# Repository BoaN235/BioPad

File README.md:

# BioPad
A 12 key macropad with a oled display and 5 LEDS uses KMK firmware. It is supposed to be a used during work to 

## Features
- 128x32 OLED Display
- KMK
- 12 Keys
- 4 Layers Currently
- 5 LEDS

## Cad Model
It fits with 4 M3 Bolts and it has 4 M1 Bolts to hold the pcb down. 
It has 3 parts the bottem the layer blocking the keys and top. 

## PCB
My PCB is 100mm by 58mm. I made it in Kicad

## Firmware
I am using KMK to be able to hotswitch it to whatever people need.
There is currently 3 layers Apps Vscode and Zoom. Each of those has hotkeys related to each app. The Apps layer types in Windows + R and adds the name of a website or app.

## BOM
Evreything I am gonna use to make it if it isen't in the kit I have it myself

- 12x Cherry MX Switches
- 12x DSA Keycaps
- 4x M3x5x4 Heatset inserts
- 4x M3x16mm SHCS Bolts
- 4x M1x5x4 Heatset inserts
- 4x M1x16mm SHCS Bolts
- 12x 1N4148 DO-35 Diodes.
- 5x WS2812B LEDs
- 1x 0.91" 128x32 OLED Display
- 1x XIAO RP2040
- 1x Case (3 printed parts I can print it myself)

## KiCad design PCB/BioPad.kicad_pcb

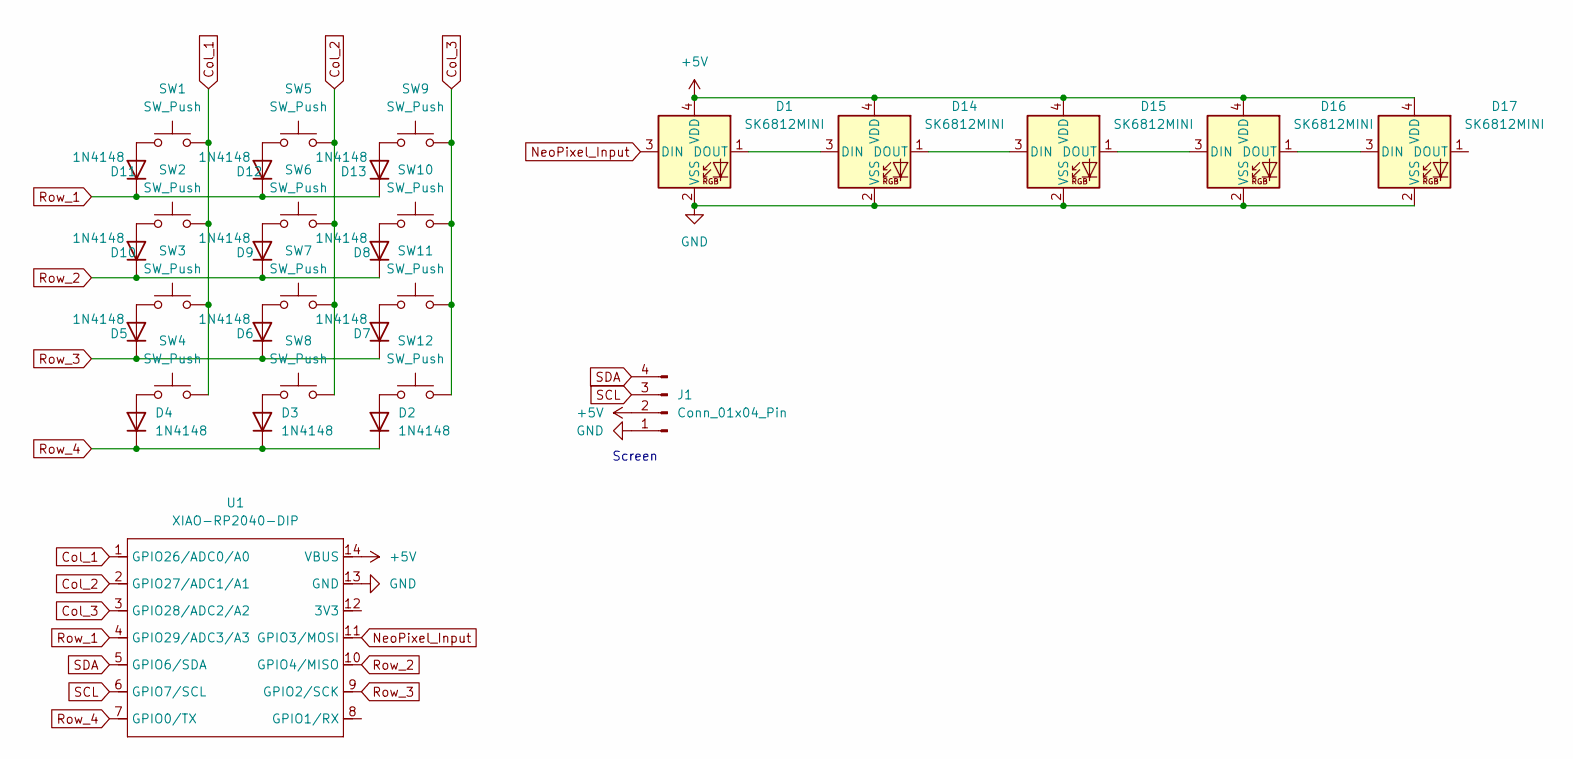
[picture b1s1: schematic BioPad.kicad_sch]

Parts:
D1, D14, D15, D16, D17: SK6812MINI; LED_SK6812MINI_PLCC4_3.5x3.5mm_P1.75mm
D2, D3, D4, D5, D6, D7, D8, D9, D10, D11, D12, D13: 1N4148; D_DO-35_SOD27_P7.62mm_Horizontal
J1: Conn_01x04_Pin; SSD1306-0.91-OLED-4pin-128x32
SW1, SW2, SW3, SW4, SW5, SW6, SW7, SW8, SW9, SW10, SW11, SW12: SW_Push; SW_Cherry_MX_1.00u_PCB
U1: XIAO-RP2040-DIP

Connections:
+5V: D1.4 (VDD), D14.4 (VDD), D15.4 (VDD), D16.4 (VDD), D17.4 (VDD), J1.2, U1.14 (VBUS)
Col_1: SW1.2, SW2.2, SW3.2, SW4.2, U1.1 (GPIO26/ADC0/A0)
Col_2: SW5.2, SW6.2, SW7.2, SW8.2, U1.2 (GPIO27/ADC1/A1)
Col_3: SW9.2, SW10.2, SW11.2, SW12.2, U1.3 (GPIO28/ADC2/A2)
GND: D1.2 (VSS), D14.2 (VSS), D15.2 (VSS), D16.2 (VSS), D17.2 (VSS), J1.1, U1.13 (GND)
NeoPixel_Input: D1.3 (DIN), U1.11 (GPIO3/MOSI)
unnamed: D1.1 (DOUT), D14.3 (DIN)
unnamed: D2.2 (A), SW12.1
unnamed: D3.2 (A), SW8.1
unnamed: D4.2 (A), SW4.1
unnamed: D5.2 (A), SW3.1
unnamed: D6.2 (A), SW7.1
unnamed: D7.2 (A), SW11.1
unnamed: D8.2 (A), SW10.1
unnamed: D9.2 (A), SW6.1
unnamed: D10.2 (A), SW2.1
unnamed: D11.2 (A), SW1.1
unnamed: D12.2 (A), SW5.1
unnamed: D13.2 (A), SW9.1
unnamed: D14.1 (DOUT), D15.3 (DIN)
unnamed: D15.1 (DOUT), D16.3 (DIN)
unnamed: D16.1 (DOUT), D17.3 (DIN)
Row_1: D11.1 (K), D12.1 (K), D13.1 (K), U1.4 (GPIO29/ADC3/A3)
Row_2: D8.1 (K), D9.1 (K), D10.1 (K), U1.10 (GPIO4/MISO)
Row_3: D5.1 (K), D6.1 (K), D7.1 (K), U1.9 (GPIO2/SCK)
Row_4: D2.1 (K), D3.1 (K), D4.1 (K), U1.7 (GPIO0/TX)
SCL: J1.3, U1.6 (GPIO7/SCL)
SDA: J1.4, U1.5 (GPIO6/SDA)

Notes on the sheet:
Screen

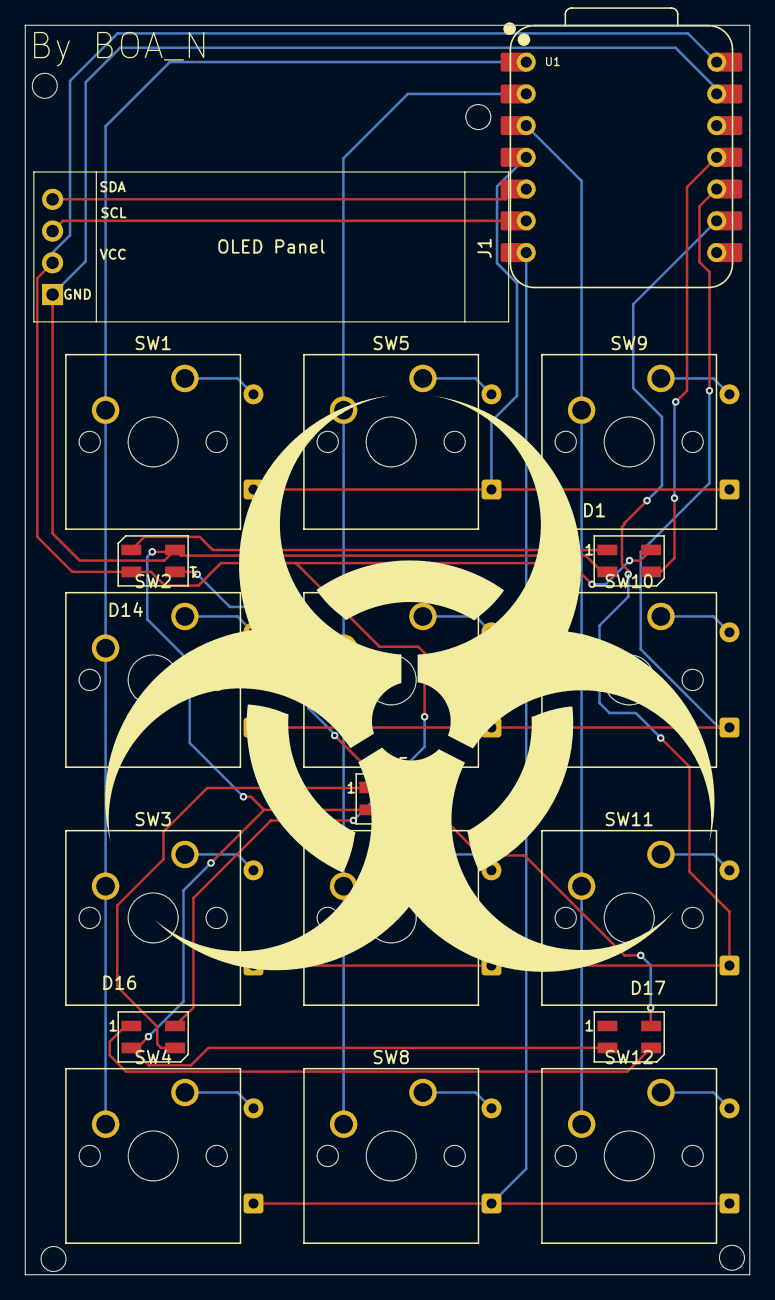
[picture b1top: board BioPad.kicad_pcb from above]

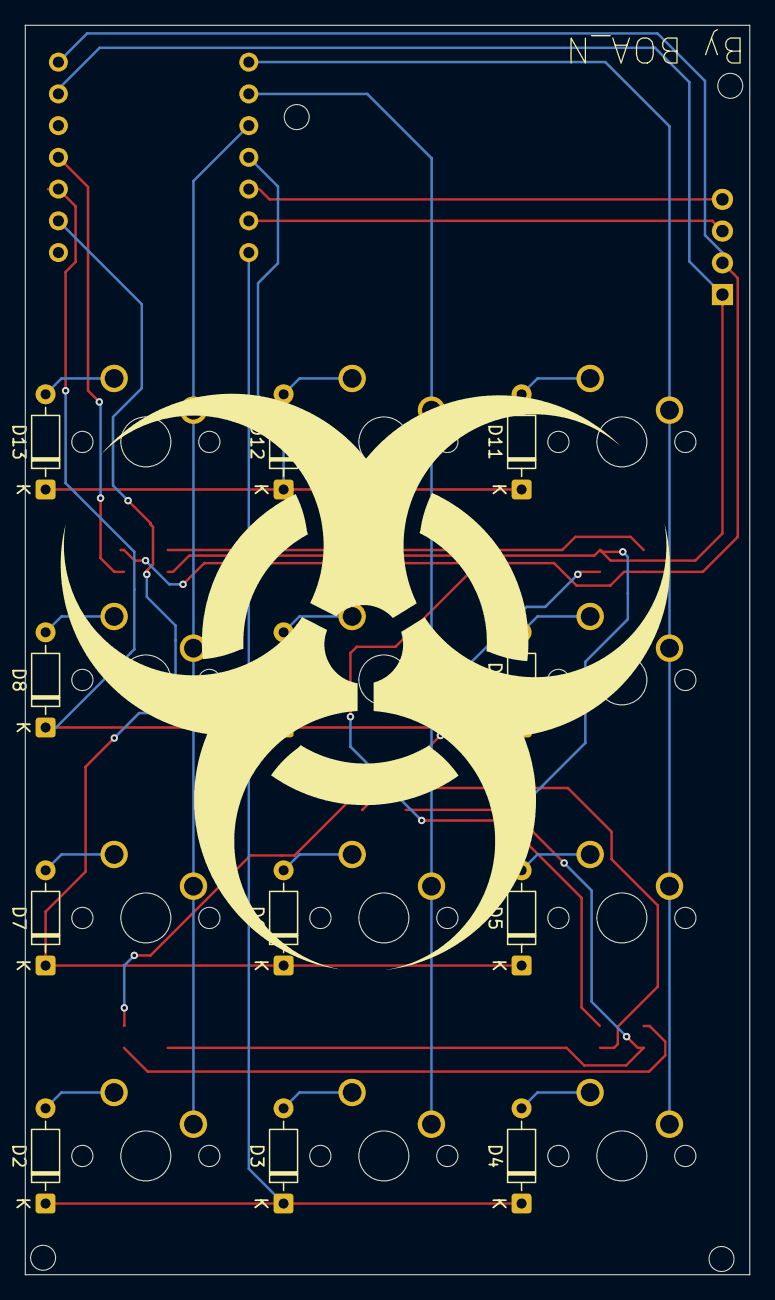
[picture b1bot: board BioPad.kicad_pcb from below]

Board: 2 copper layers, 58.0 x 100.0 mm, 31 parts (12 on the bottom side), 28 nets.

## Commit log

2026-01-13 init commit
2026-01-13 Add initial README for BioPad project
    Added detailed information about the BioPad project, including features, CAD model, PCB specifications, firmware, and bill of materials.
